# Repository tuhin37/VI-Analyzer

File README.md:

# VI-Analyzer
VI-Analyzer measures DC parameters like terminal voltage and load current with great precesion and loggs them

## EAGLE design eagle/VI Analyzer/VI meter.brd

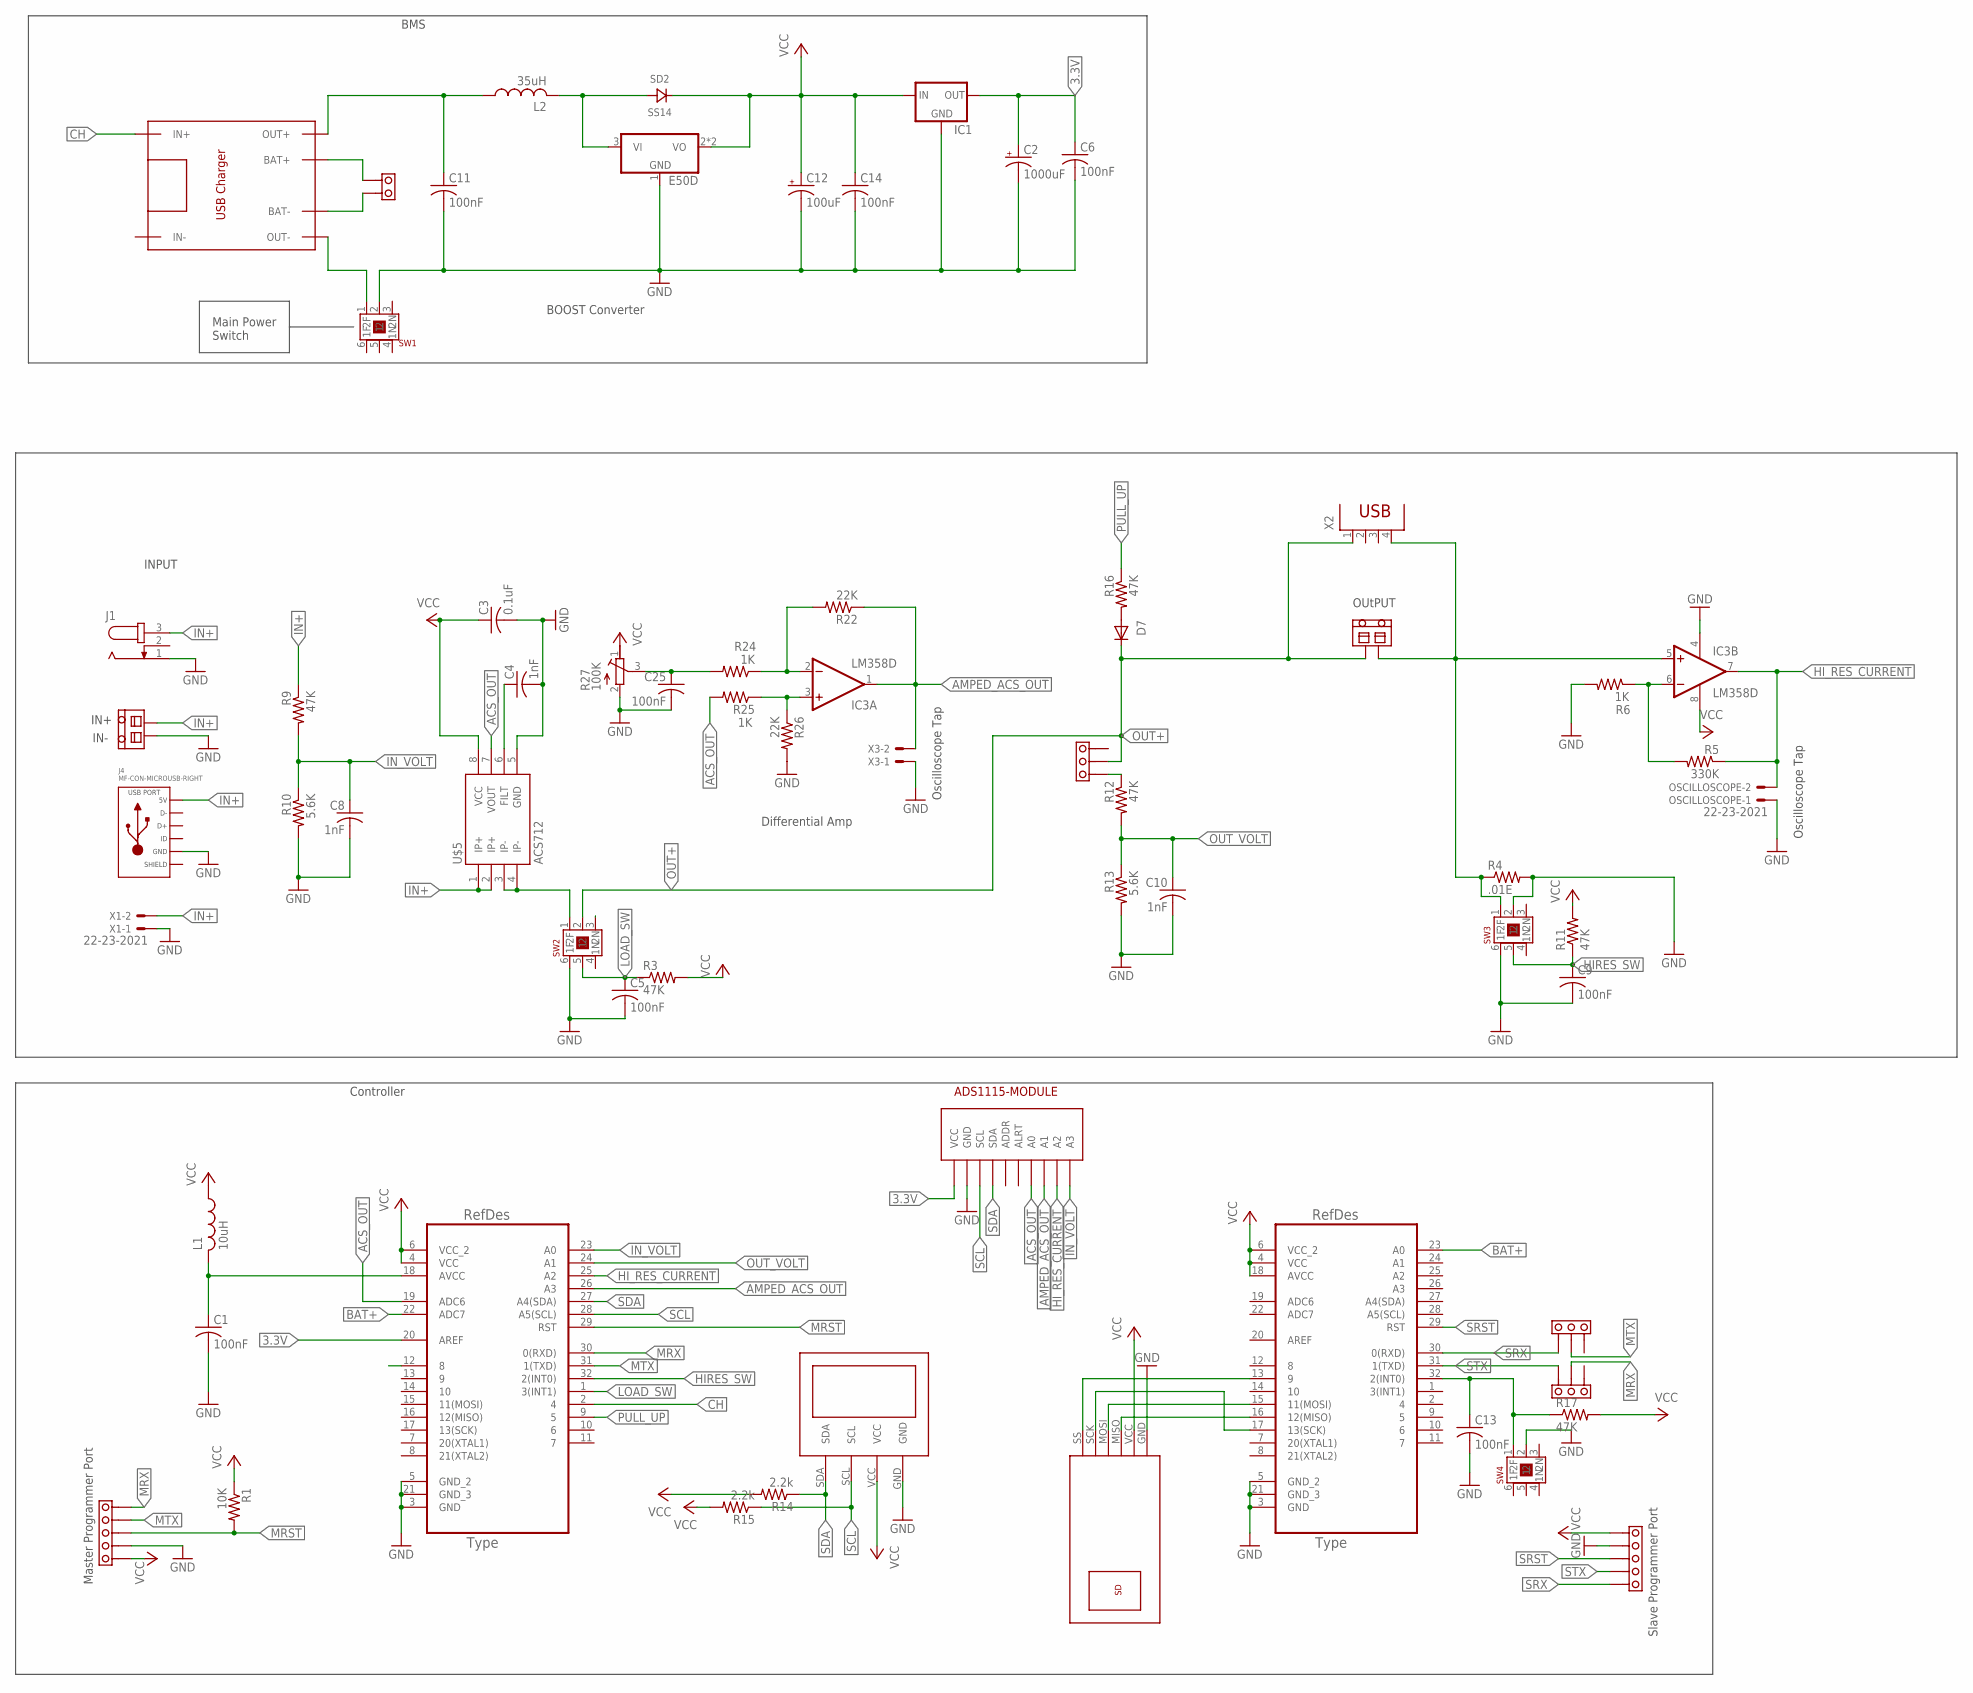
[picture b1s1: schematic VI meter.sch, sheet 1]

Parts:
C1, C5, C6, C9, C11, C13, C14, C25: 100nF; C1206
C2: 1000uF; 153CLV-0807
C3: 0.1uF; C1206
C4, C8, C10: 1nF; C1206
C12: 100uF; 150CLZ-0810
D7: DIODE-MINIMELF; MINIMELF
IC1: LM1117; SOT223
IC2: E50D; SOT89
IC3: LM358D; SO08
J1: JACK-PLUG1; SPC4078
J4: MF-CON-MICROUSB-RIGHT; MICROUSB-RIGHT
L1: 10uH; 0207/10
L2: 35uH; POWER-CHOKE_WE-TPC
OSCILLOSCOPE: 22-23-2021
R1: 10K; M1206
R3, R9, R11, R12, R16, R17: 47K; M1206
R4: .01E; 0617/17
R5: 330K; M1206
R6, R24, R25: 1K; M1206
R10, R13: 5.6K; M1206
R14, R15: 2.2k; M1206
R22, R26: 22K; M1206
R27: 100K; 3386P
SD2: SS14; DO214
SW1: PUSH_LATCH_SW_9X9
SW2: Load Switch; PUSH_LATCH_SW_9X9
SW3, SW4: Hi Res; PUSH_LATCH_SW_9X9
U$1, U$3: TERMINAL_BLOCK
U$2: MASTER; QFP80P900X900X120-32N
U$4, U$11: BERG_5
U$5: ACS712; SO08
U$6: TP4056
U$7: BERG_2
U$8, U$14, U$15: BERG_3
U$9: SLAVE; QFP80P900X900X120-32N
U$10: MICROSD_ARDUINO
U$12: OLED_0.96
U$13: ADS1115-MODULE
X1, X3: 22-23-2021
X2: PN87520

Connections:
3.3V: C2.+, C6.1, IC1.2 (OUT), U$2.20 (AREF), U$13.VCC
ACS_OUT: R25.2, U$2.19 (ADC6), U$5.7 (VOUT), U$13.A0
AMPED_ACS_OUT: IC3.1 (OUT), R22.1, U$2.26 (A3), U$13.A1, X3.2
BAT+: U$2.22 (ADC7), U$6.BAT+, U$7.F, U$9.23 (A0)
BAT-: U$6.BAT-, U$7.E
BOUT+: C11.1, L2.1, U$6.OUT+
CH: U$2.2 (4), U$2.12 (8), U$6.IN+
GND: C1.2, C2.-, C3.2, C4.2, C5.2, C6.2, C8.2, C9.2, C10.2, C11.2, C12.-, C13.2, C14.2, C25.2, IC1.1 (GND), IC2.1 (GND), IC3.4 (V-), J1.1, J4.5 (GND), OSCILLOSCOPE.1, R4.2, R6.2, R10.2, R13.2, R26.2, R27.2, SW1.2 (1), SW2.6 (2F), SW3.2 (1), SW3.6 (2F), SW4.2 (1), U$1.2, U$2.3 (GND), U$2.5 (GND_2), U$2.21 (GND_3), U$4.H, U$5.5 (GND), U$9.3 (GND), U$9.5 (GND_2), U$9.21 (GND_3), U$10.GND, U$11.H, U$12.GND, U$13.GND, X1.1, X3.1
HIRES_SW: C9.1, R11.1, SW3.5 (2), U$2.32 (2(INT0))
HI_RES_CURRENT: IC3.7 (OUT), OSCILLOSCOPE.2, R5.1, U$2.25 (A2), U$13.A2
IN+: J1.3, J4.1 (5V), R9.1, U$1.1, U$5.1 (IP+), U$5.2 (IP+), X1.2
IN_VOLT: C8.1, R9.2, R10.1, U$2.23 (A0), U$13.A3
LOAD-: IC3.5 (+IN), R4.1, SW3.1 (1F), U$3.1, X2.4
LOAD_SW: C5.1, R3.1, SW2.5 (2), U$2.1 (3(INT1))
MRST: R1.2, U$2.29 (RST), U$4.G
MRX: U$2.30 (0(RXD)), U$4.E, U$15.F
MTX: U$2.31 (1(TXD)), U$4.F, U$14.F
unnamed: C1.1, L1.2, U$2.18 (AVCC)
unnamed: IC2.3 (VI), L2.2, SD2.ANODE
unnamed: C4.1, U$5.6 (FILT)
unnamed: IC3.6 (-IN), R5.2, R6.1
unnamed: R12.1, U$8.G
unnamed: SW2.1 (1F), U$5.3 (IP-), U$5.4 (IP-)
unnamed: U$9.16 (12(MISO)), U$10.MISO
unnamed: U$9.15 (11(MOSI)), U$10.MOSI
unnamed: U$9.17 (13(SCK)), U$10.SCK
unnamed: D7.A, R16.2
unnamed: U$9.13 (9), U$10.SS (CS)
unnamed: C13.1, R17.1, SW4.1 (1F), U$9.32 (2(INT0))
unnamed: IC3.2 (-IN), R22.2, R24.1
unnamed: IC3.3 (+IN), R25.1, R26.1
OUT+: D7.C, SW2.2 (1), U$3.2, U$8.F, X2.1
OUT-: SW1.1 (1F), U$6.OUT-
OUT_VOLT: C10.1, R12.2, R13.1, U$2.24 (A1)
POT_OFFSET: C25.1, R24.2, R27.3
PULL_UP: R16.1, U$2.9 (5)
SCL: R15.1, U$2.28 (A5(SCL)), U$12.SCL, U$13.SCL
SDA: R14.1, U$2.27 (A4(SDA)), U$12.SDA, U$13.SDA
SLD: J4.S1 (SLD), J4.S2 (SLD), J4.S3 (SLD), J4.S4 (SLD), J4.S5 (SLD), J4.S6 (SLD)
SRST: U$9.29 (RST), U$11.G
SRX: U$9.30 (0(RXD)), U$11.E, U$14.G
STX: U$9.31 (1(TXD)), U$11.F, U$15.E
VCC: C3.1, C12.+, C14.1, IC1.3 (IN), IC2.2 (VO), IC2.2@1 (VO), IC3.8 (V+), L1.1, R1.1, R3.2, R11.2, R14.2, R15.2, R17.2, R27.1, SD2.CATHODE, U$2.4 (VCC), U$2.6 (VCC_2), U$4.I, U$5.8 (VCC), U$9.4 (VCC), U$9.6 (VCC_2), U$9.18 (AVCC), U$10.VCC, U$11.I, U$12.VCC

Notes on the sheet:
BOOST Converter
Main Power Switch
Master Programmer Port
INPUT
IN+
IN-
BMS
Controller
OUtPUT
Differential Amp
Slave Programmer Port
Oscilloscope Tap

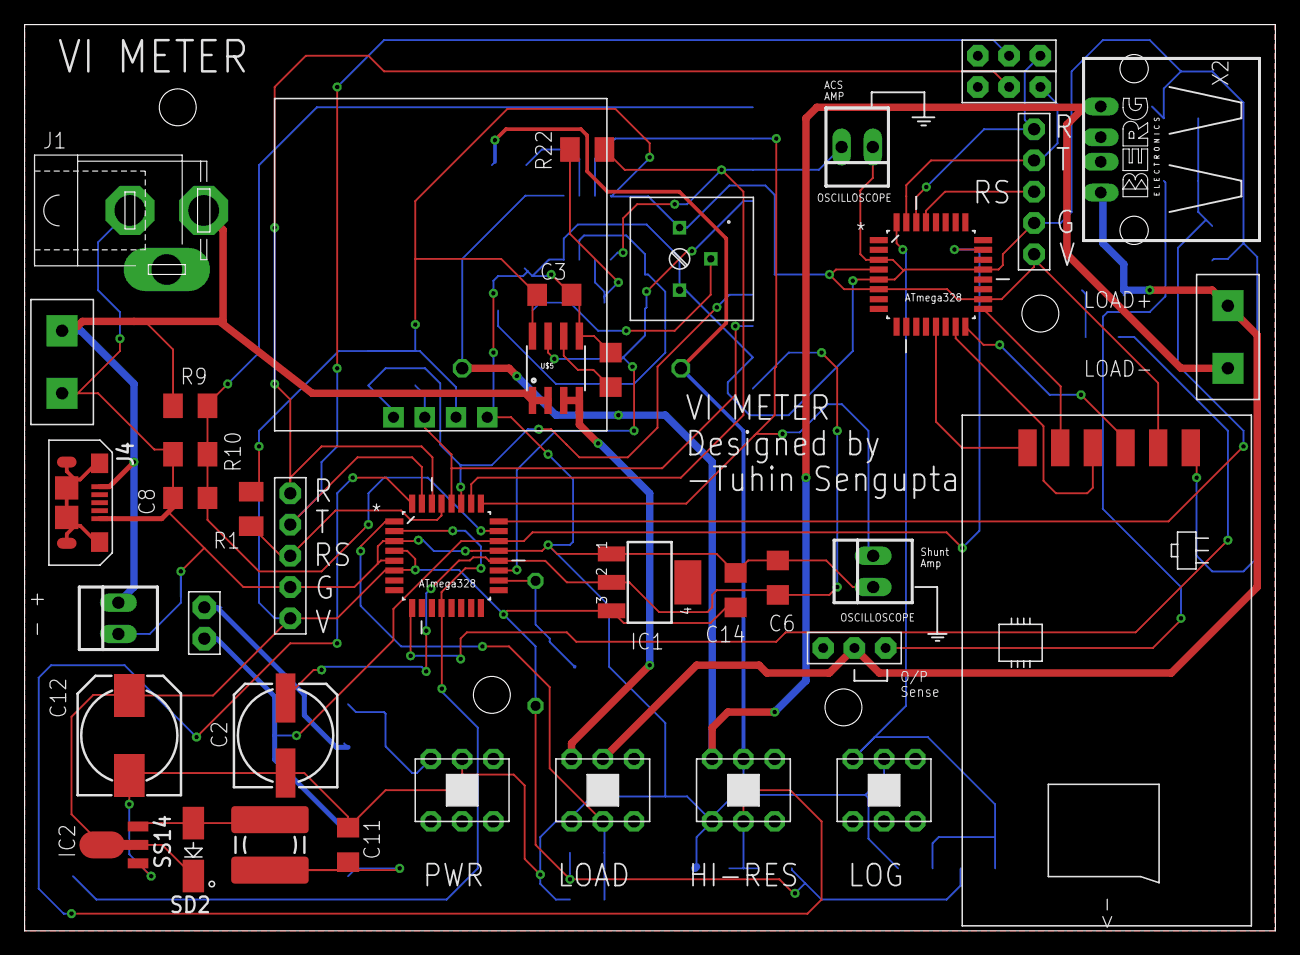
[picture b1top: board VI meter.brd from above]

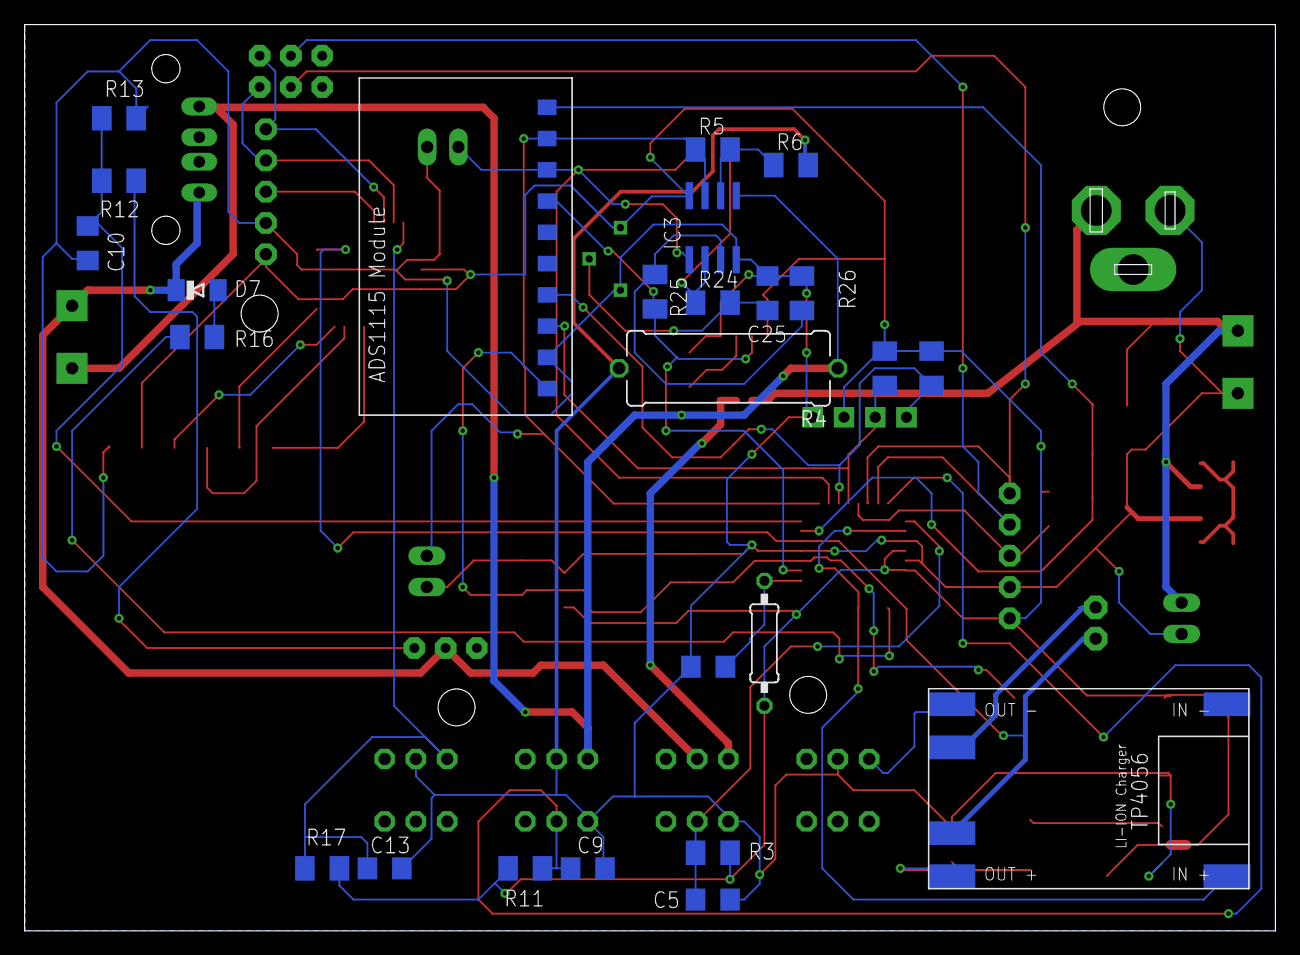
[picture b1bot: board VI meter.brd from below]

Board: 2 copper layers, 101.7 x 73.7 mm, 65 parts (25 on the bottom side), 43 nets.

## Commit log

2018-08-29 ADD: Initial adding of existing files
2018-08-30 ADD: mWh reading during Load on and load off EDIT: Virtical allignment of load and source data
2018-08-30 EDIT: Allignment of Current value EDIT: Extended the range of resistances ADD: 'OPEN' and 'SHORT' Display for resistance when out of range
2018-09-03 ADD: Hi res current reading from ads1115
2018-09-03 Test
2018-12-06 Fix: moved the shunt to the lower side, single channel amp instead of differential
2018-12-23 Edit: fixed source voltage, can be improved with more granular peice-wise equations
2019-08-07 Add: additional files

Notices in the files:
parts and their libraries:
SparkFun-AnalogIC: Licensing: CC v3.0 Share-Alike You are welcome to use this library for commercial purposes.
